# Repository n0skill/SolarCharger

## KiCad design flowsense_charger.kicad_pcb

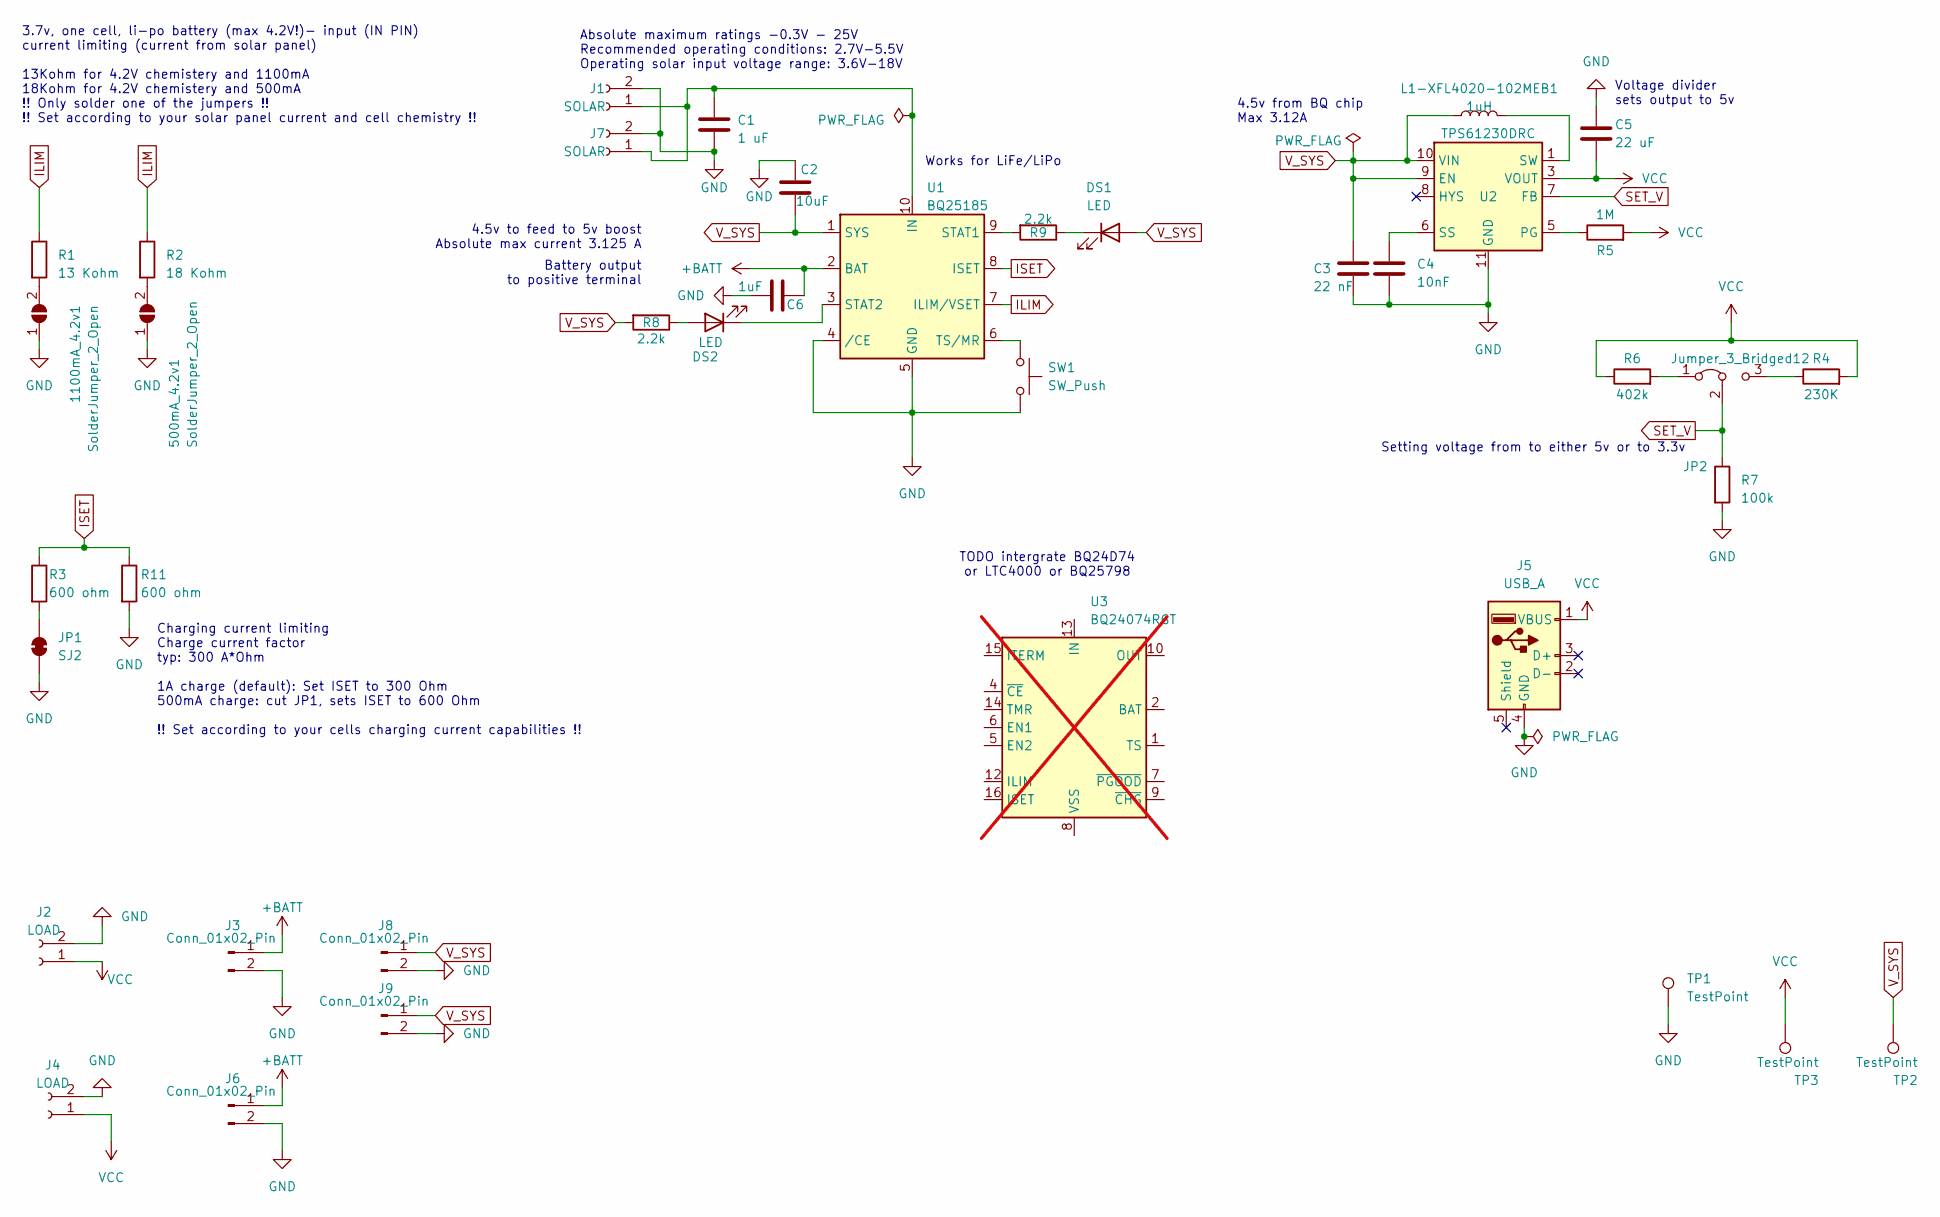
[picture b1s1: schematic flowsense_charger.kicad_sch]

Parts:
500mA_4.2v1, 1100mA_4.2v1: SolderJumper_2_Open; SolderJumper-2_P1.3mm_Open_Pad1.0x1.5mm
C1: 1 uF; C_0805_2012Metric
C2: 10uF; C_0805_2012Metric
C3: 22 nF; C_0805_2012Metric
C4: 10nF; C_0805_2012Metric
C5: 22 uF; C_0805_2012Metric
C6: 1uF; C_0805_2012Metric
DS1, DS2: LED; LED_1206_3216Metric_Pad1.42x1.75mm_HandSolder
J1: SOLAR; JST_PH_B2B-PH-K_1x02_P2.00mm_Vertical
J2: LOAD; JST_PH_B2B-PH-K_1x02_P2.00mm_Vertical
J3, J8: Conn_01x02_Pin; JST_PH_B2B-PH-K_1x02_P2.00mm_Vertical
J4: LOAD; TerminalBlock_Phoenix_MPT-0,5-2-2.54_1x02_P2.54mm_Horizontal
J5: USB_A; USB_Micro-B_Molex-105017-0001
J6, J9: Conn_01x02_Pin; TerminalBlock_Phoenix_MPT-0,5-2-2.54_1x02_P2.54mm_Horizontal
J7: SOLAR; TerminalBlock_Phoenix_MPT-0,5-2-2.54_1x02_P2.54mm_Horizontal
JP1: SJ2; SolderJumper-2_P1.3mm_Bridged_Pad1.0x1.5mm
JP2: Jumper_3_Bridged12; PinHeader_1x03_P2.54mm_Vertical
L1-XFL4020-102MEB1: 1uH; L_Coilcraft_XxL4020
R1: 13 Kohm; R_1206_3216Metric
R2: 18 Kohm; R_1206_3216Metric
R3, R11: 600 ohm; R_1206_3216Metric
R4: 230K; R_1206_3216Metric
R5: 1M; R_1206_3216Metric
R6: 402k; R_1206_3216Metric
R7: 100k; R_1206_3216Metric
R8, R9: 2.2k; R_1206_3216Metric
SW1: SW_Push; SW_PUSH_6mm
TP1, TP2, TP3: TestPoint; TestPoint_Pad_D1.0mm
U1: BQ25185; WSON-10-1EP_2.5x2.5mm_P0.5mm_EP1.2x2mm
U2: TPS61230DRC; Texas_S-PVSON-N10_ThermalVias
U3: BQ24074RGT; VQFN-16-1EP_3x3mm_P0.5mm_EP1.6x1.6mm; not fitted

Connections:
+BATT: C6.2, J3.1, J6.1, U1.2 (BAT)
GND: 500mA_4.2v1.1 (A), 1100mA_4.2v1.1 (A), C1.2, C2.2, C3.2, C4.2, C5.1, C6.1, J1.2, J2.2, J3.2, J4.2, J5.4 (GND), J6.2, J7.2, J8.2, J9.2, JP1.1 (A), R7.2, R11.2, SW1.2, TP1.1, U1.4 (/CE), U1.5 (GND), U2.11 (GND)
ILIM: R1.1, R2.1, U1.7 (ILIM/VSET)
ISET: R3.1, R11.1, U1.8 (ISET)
unnamed: 500mA_4.2v1.2 (B), R2.2
unnamed: 1100mA_4.2v1.2 (B), R1.2
unnamed: DS1.1 (K), R9.1
unnamed: DS2.2 (A), R8.1
unnamed: DS2.1 (K), U1.3 (STAT2)
unnamed: C1.1, J1.1, J7.1, U1.10 (IN)
unnamed: JP1.2 (B), R3.2
unnamed: JP2.1 (A), R6.2
unnamed: JP2.3 (B), R4.1
unnamed: L1-XFL4020-102MEB1.2, U2.1 (SW), U2.2 (SW)
unnamed: R9.2, U1.9 (STAT1)
unnamed: SW1.1, U1.6 (TS/MR)
unnamed: R5.1, U2.5 (PG)
unnamed: C4.1, U2.6 (SS)
unnamed: U3.2 (BAT), U3.3 (BAT)
unnamed: U3.10 (OUT), U3.11 (OUT)
unnamed: U3.8 (VSS), U3.17 (VSS)
SET_V: JP2.2 (C), R7.1, U2.7 (FB)
VCC: C5.2, J2.1, J4.1, J5.1 (VBUS), R4.2, R5.2, R6.1, TP3.1, U2.3 (VOUT), U2.4 (VOUT)
V_SYS: C2.1, C3.1, DS1.2 (A), J8.1, J9.1, L1-XFL4020-102MEB1.1, R8.2, TP2.1, U1.1 (SYS), U2.9 (EN), U2.10 (VIN)

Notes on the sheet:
Absolute maximum ratings -0.3V - 25V Recommended operating conditions: 2.7V-5.5V Operating solar input voltage range: 3.6V-18V
Charging current limiting Charge current factor typ: 300 A*Ohm 1A charge (default): Set ISET to 300 Ohm 500mA charge: cut JP1, sets ISET to 600 Ohm !! Set according to your cells charging current capabilities !!
3.7v, one cell, li-po battery (max 4.2V!)- input (IN PIN) current limiting (current from solar panel) 13Kohm for 4.2V chemistery and 1100mA 18Kohm for 4.2V chemistery and 500mA !! Only solder one of the jumpers !! !! Set according to your solar panel current and cell chemistry !!
Voltage divider sets output to 5v
4.5v from BQ chip Max 3.12A
TODO intergrate BQ24D74 or LTC4000 or BQ25798
4.5v to feed to 5v boost Absolute max current 3.125 A
Setting voltage from to either 5v or to 3.3v
Battery output to positive terminal
Works for LiFe/LiPo

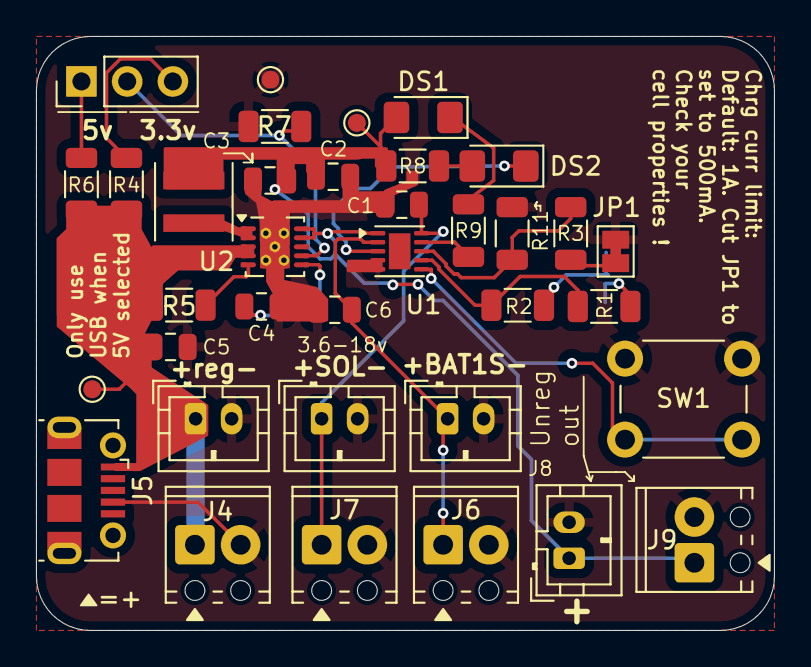
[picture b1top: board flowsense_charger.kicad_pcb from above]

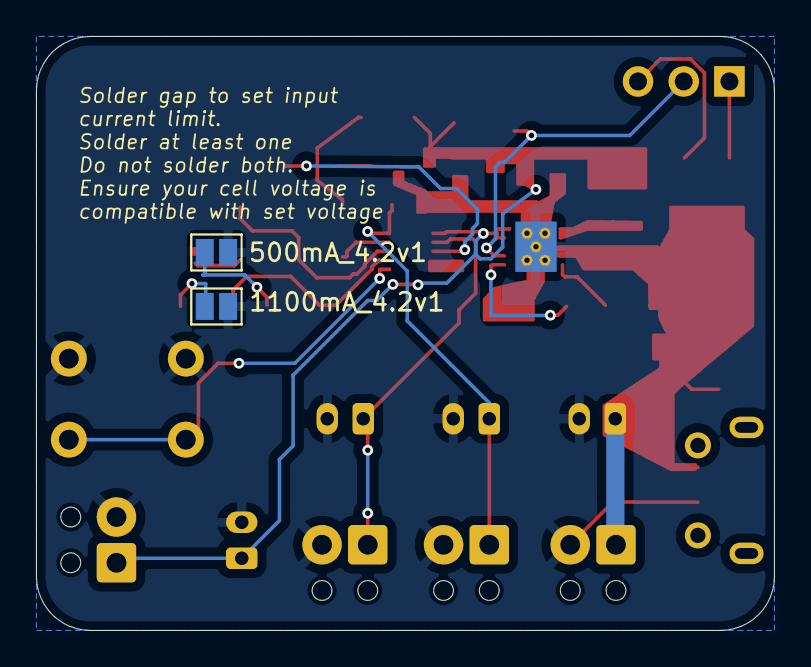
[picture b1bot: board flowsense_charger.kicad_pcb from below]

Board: 2 copper layers, 41.0 x 33.0 mm, 38 parts (2 on the bottom side), 21 nets.

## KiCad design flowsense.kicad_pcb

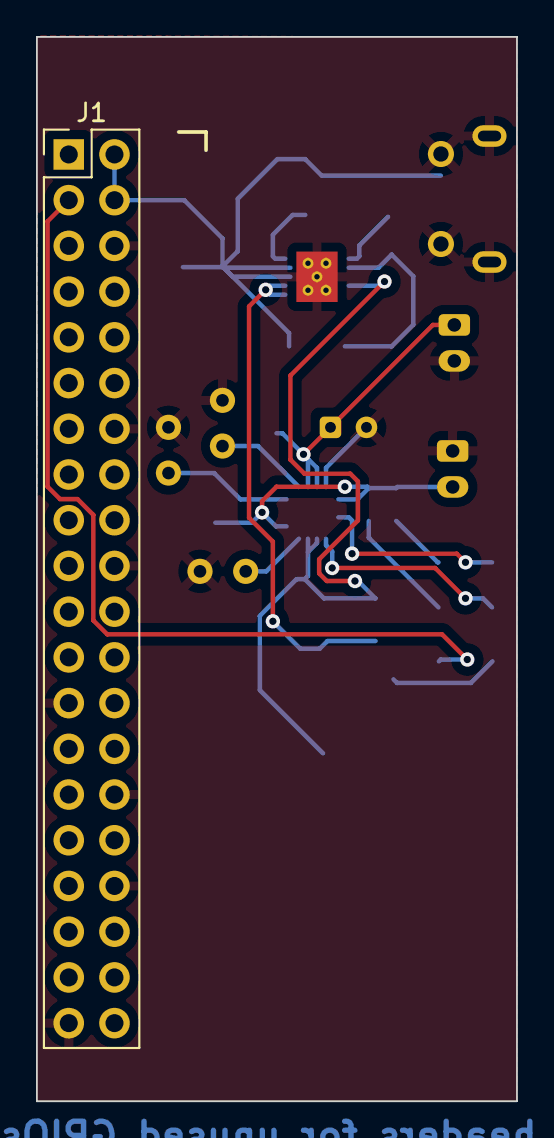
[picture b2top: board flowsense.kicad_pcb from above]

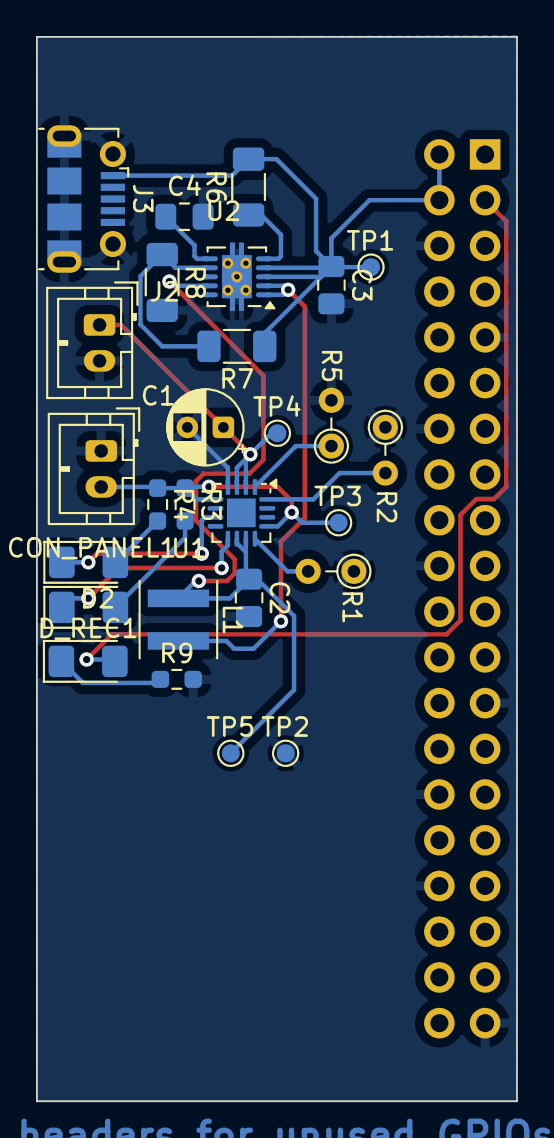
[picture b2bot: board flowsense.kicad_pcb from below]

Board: 2 copper layers, 26.7 x 59.1 mm, 28 parts (27 on the bottom side), 18 nets.

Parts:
C1: 4.7u; CP_Radial_D4.0mm_P2.00mm
C2: 22 nF; C_0805_2012Metric_Pad1.18x1.45mm_HandSolder
C3: 22 uF; C_0805_2012Metric_Pad1.18x1.45mm_HandSolder
C4: 10nF; C_0805_2012Metric_Pad1.18x1.45mm_HandSolder
CON_PANEL1: Conn_01x02_Pin; JST_PH_B2B-PH-K_1x02_P2.00mm_Vertical
D1, D2: LED; LED_1206_3216Metric_Pad1.42x1.75mm_HandSolder
D_REC1: LED; LED_1206_3216Metric_Pad1.42x1.75mm_HandSolder
J1: Conn_02x20_Odd_Even; PinHeader_2x20_P2.54mm_Vertical
J2: Conn_01x02_Pin; JST_PH_B2B-PH-K_1x02_P2.00mm_Vertical
J3: USB_B_Micro; USB_Micro-B_Molex-105017-0001
L1: 1uH; L_Coilcraft_XxL4020
R1: 1.1k; R_Axial_DIN0204_L3.6mm_D1.6mm_P2.54mm_Vertical
R2: 590; R_Axial_DIN0204_L3.6mm_D1.6mm_P2.54mm_Vertical
R3, R4, R9: 470; R_0603_1608Metric_Pad0.98x0.95mm_HandSolder
R5: 10k; R_Axial_DIN0204_L3.6mm_D1.6mm_P2.54mm_Vertical
R6: 1M; R_1206_3216Metric_Pad1.30x1.75mm_HandSolder
R7: 402k; R_1206_3216Metric_Pad1.30x1.75mm_HandSolder
R8: 100k; R_1206_3216Metric_Pad1.30x1.75mm_HandSolder
TP1, TP2, TP3, TP4, TP5: TestPoint; TestPoint_Pad_D1.0mm
U1: BQ24074RGT; VQFN-16-1EP_3x3mm_P0.5mm_EP1.6x1.6mm
U2: TPS61230DRC; Texas_S-PVSON-N10_ThermalVias

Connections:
+5V: C3.1, J1.2, J1.4, J3.1 (VBUS), R6.2, R7.1, TP1.1, U2.3 (VOUT), U2.4 (VOUT)
+BATT: C1.1, J2.1, TP4.1, U1.2 (BAT), U1.3 (BAT)
GND: C1.2, C2.2, C3.2, C4.2, CON_PANEL1.1, J1.6, J1.9, J1.14, J1.20, J1.25, J1.30, J1.34, J1.39, J2.2, J3.5 (GND), J3.6 (Shield), R1.1, R2.1, R5.2, R8.2, R9.2, TP2.1, U1.4 (~CE), U1.6 (EN1), U1.8 (VSS), U1.17 (VSS), U2.11 (GND)
unnamed: D1.2 (A), R3.2
unnamed: D1.1 (K), U1.9 (~CHG)
unnamed: D2.2 (A), R4.2
unnamed: D2.1 (K), U1.7 (~PGOOD)
unnamed: D_REC1.2 (A), J1.3
unnamed: D_REC1.1 (K), R9.1
unnamed: L1.2, U2.1 (SW), U2.2 (SW)
unnamed: R1.2, U1.12 (ILIM)
unnamed: R2.2, U1.16 (ISET)
unnamed: R5.1, U1.1 (TS)
unnamed: R7.2, R8.1, U2.7 (FB)
unnamed: R6.1, U2.5 (PG)
unnamed: C4.1, U2.6 (SS)
VDD: CON_PANEL1.2, R3.1, R4.1, TP3.1, U1.5 (EN2), U1.13 (IN)
VIN_BOOST: C2.1, L1.1, TP5.1, U1.10 (OUT), U1.11 (OUT), U2.9 (EN), U2.10 (VIN)

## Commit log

2025-06-02 Adds initial files
2025-06-02 Updating readme to describe the project a little bit more
2026-01-07 Scheme: Fixes capacitor issue on PIN1 SYS of U1. Adds decoupler 1uF on PIN2 BAT of U1. Clarifies text
2026-01-07 Writing more info on the readme
2026-01-09 Starts implementing non-regulated output, and alternative 3.3v regulated output.
2026-01-09 Rearrange text on schematic a bit
2026-01-16 Layout all components on a single face for easier manufacturing
2026-01-19 Removes old design file. Updates current file with design that passes DRC.
2026-01-19 Adds render to the project
2026-01-19 Fixes image readme
2026-01-19 typo fix in readme
2026-01-20 Updates readme with latest info. Updates silkscreen infos. Ignore thermal relief warnings. Champfer board edges
2026-01-20 Apply last commit chages to the non-cache files. Error check passes.
2026-01-20 Adds updated renders of the board, now including back side
